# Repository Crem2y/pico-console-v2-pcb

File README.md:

# Pico console V2 Board

A custom handheld console platform built around dual RP2350 microcontrollers, featuring a dedicated main processor and southbridge.

The board integrates a display, audio system, game controls, sensors, and external interfaces, with communication between the two MCUs.

**Note:** This board requires a separate [RP2350A Main Board](https://github.com/Crem2y/rp2350a_main_board) to operate.

## Specifications

- **Main MCU:** Raspberry Pi RP2350A
- **Southbridge MCU:** Raspberry Pi RP2350B
- **Flash:** 1-16 MB
- **Display:** 480x320 LCD with touch panel
- **Audio:** Stereo speakers, 3.5 mm audio jack
- **Controls:** Dual analog sticks, D-pad, face buttons, and additional function buttons
- **Sensors:** 6-axis IMU
- **Haptics:** Dual LRA actuators
- **Communication:** UART-based inter-MCU communication
- **External interfaces:** IR transceiver, Qwiic/ST connector
- **Expansion:** 10-pin FPC connector (0.5 mm pitch), additional GPIO/ADC pads
- **Power inputs:** VUSB (1.8-5.5 V), BAT (3.0-4.2 V)
- **Debug:** SWD interfaces

## Pinout

## Schematics

# PCB

## Design Files

- **EDA:** KiCad 9.0
- PCB design and schematic source files are available in this repository.

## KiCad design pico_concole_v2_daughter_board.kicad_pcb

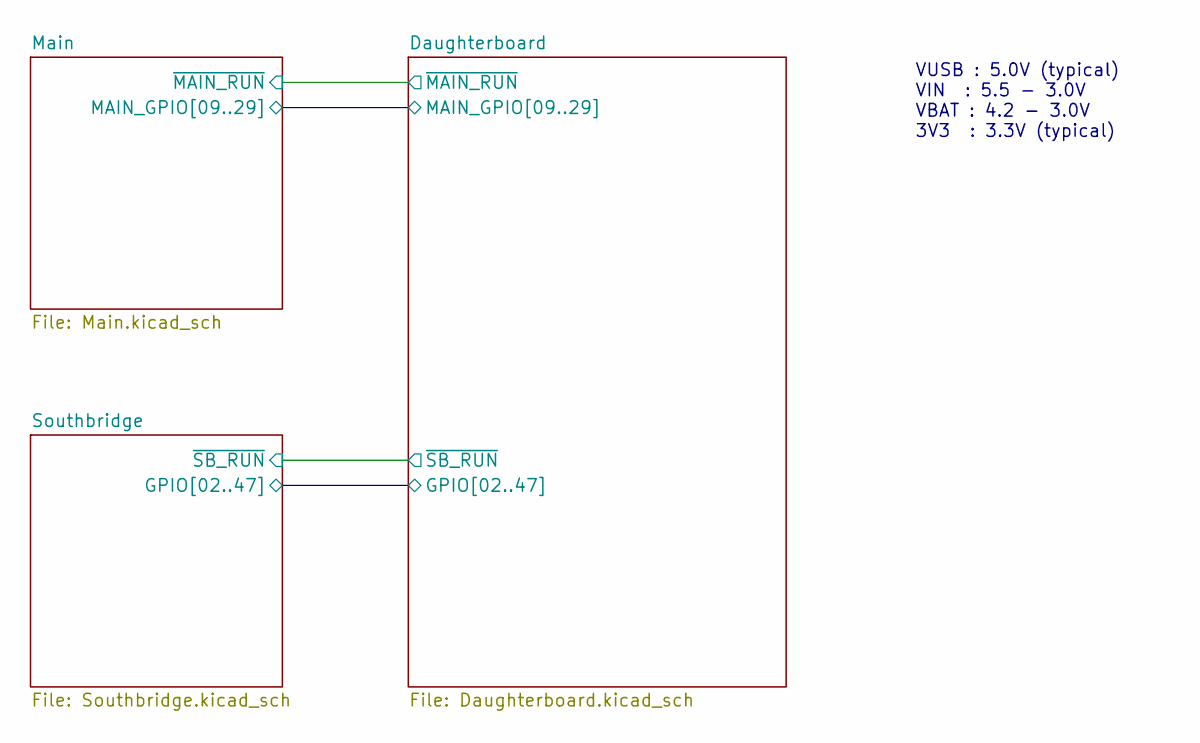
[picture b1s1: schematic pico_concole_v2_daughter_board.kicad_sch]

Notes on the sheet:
VUSB : 5.0V (typical) VIN : 5.5 - 3.0V VBAT : 4.2 - 3.0V 3V3 : 3.3V (typical)

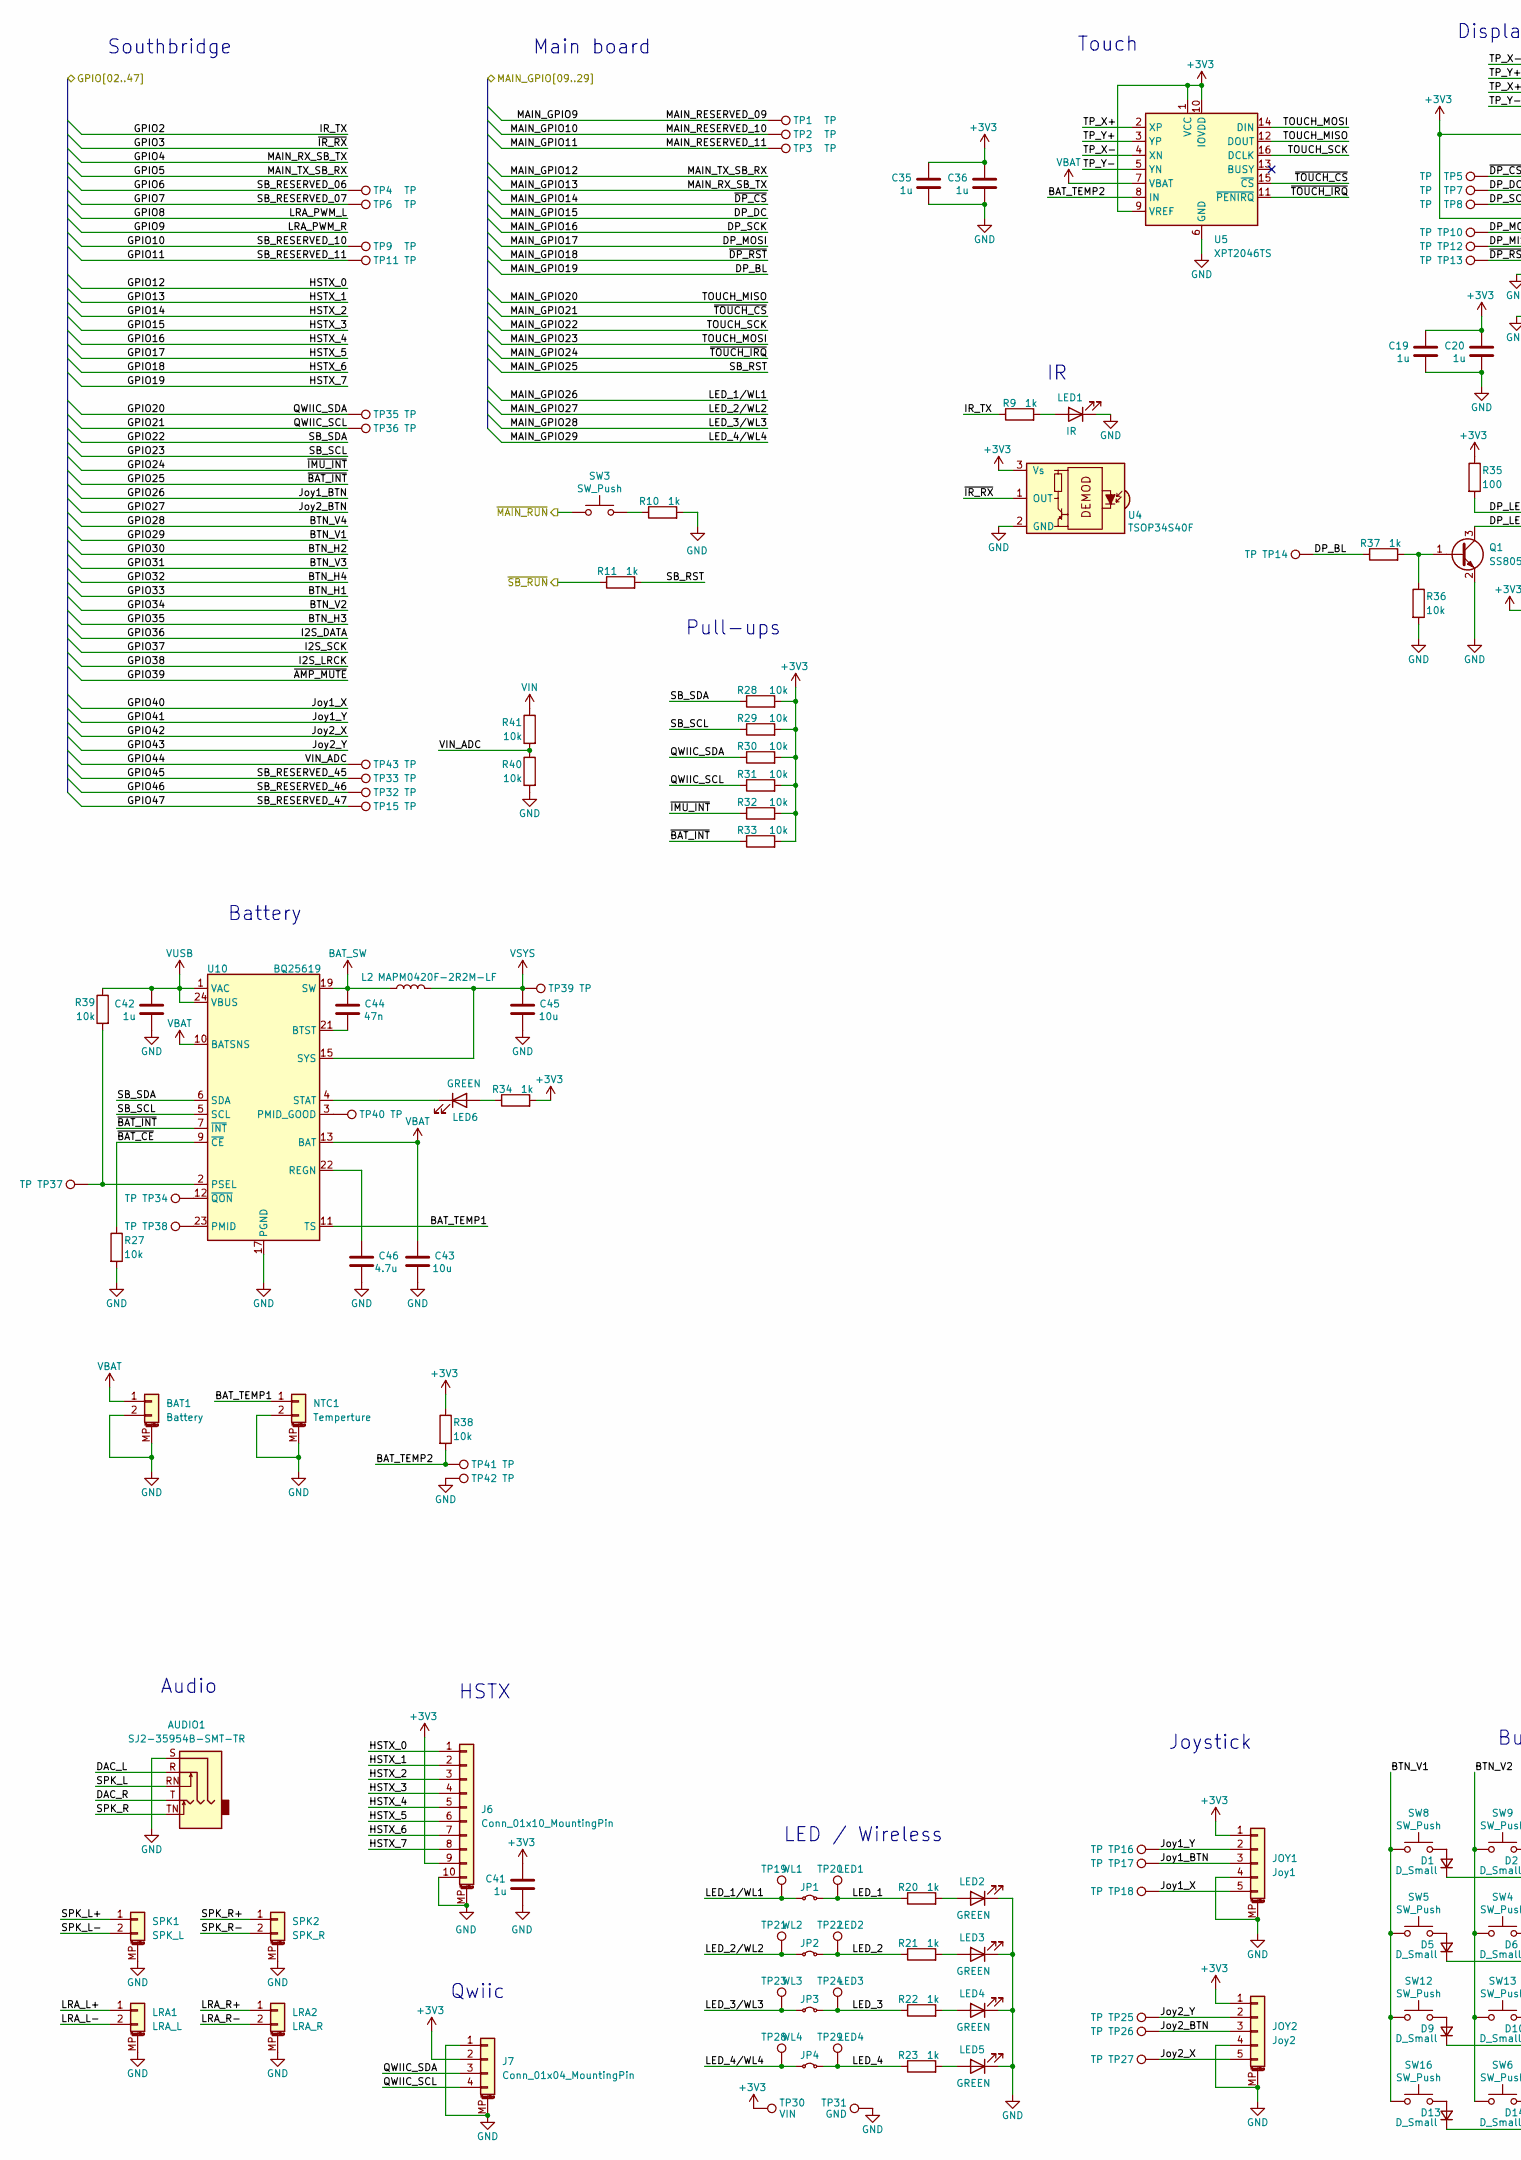
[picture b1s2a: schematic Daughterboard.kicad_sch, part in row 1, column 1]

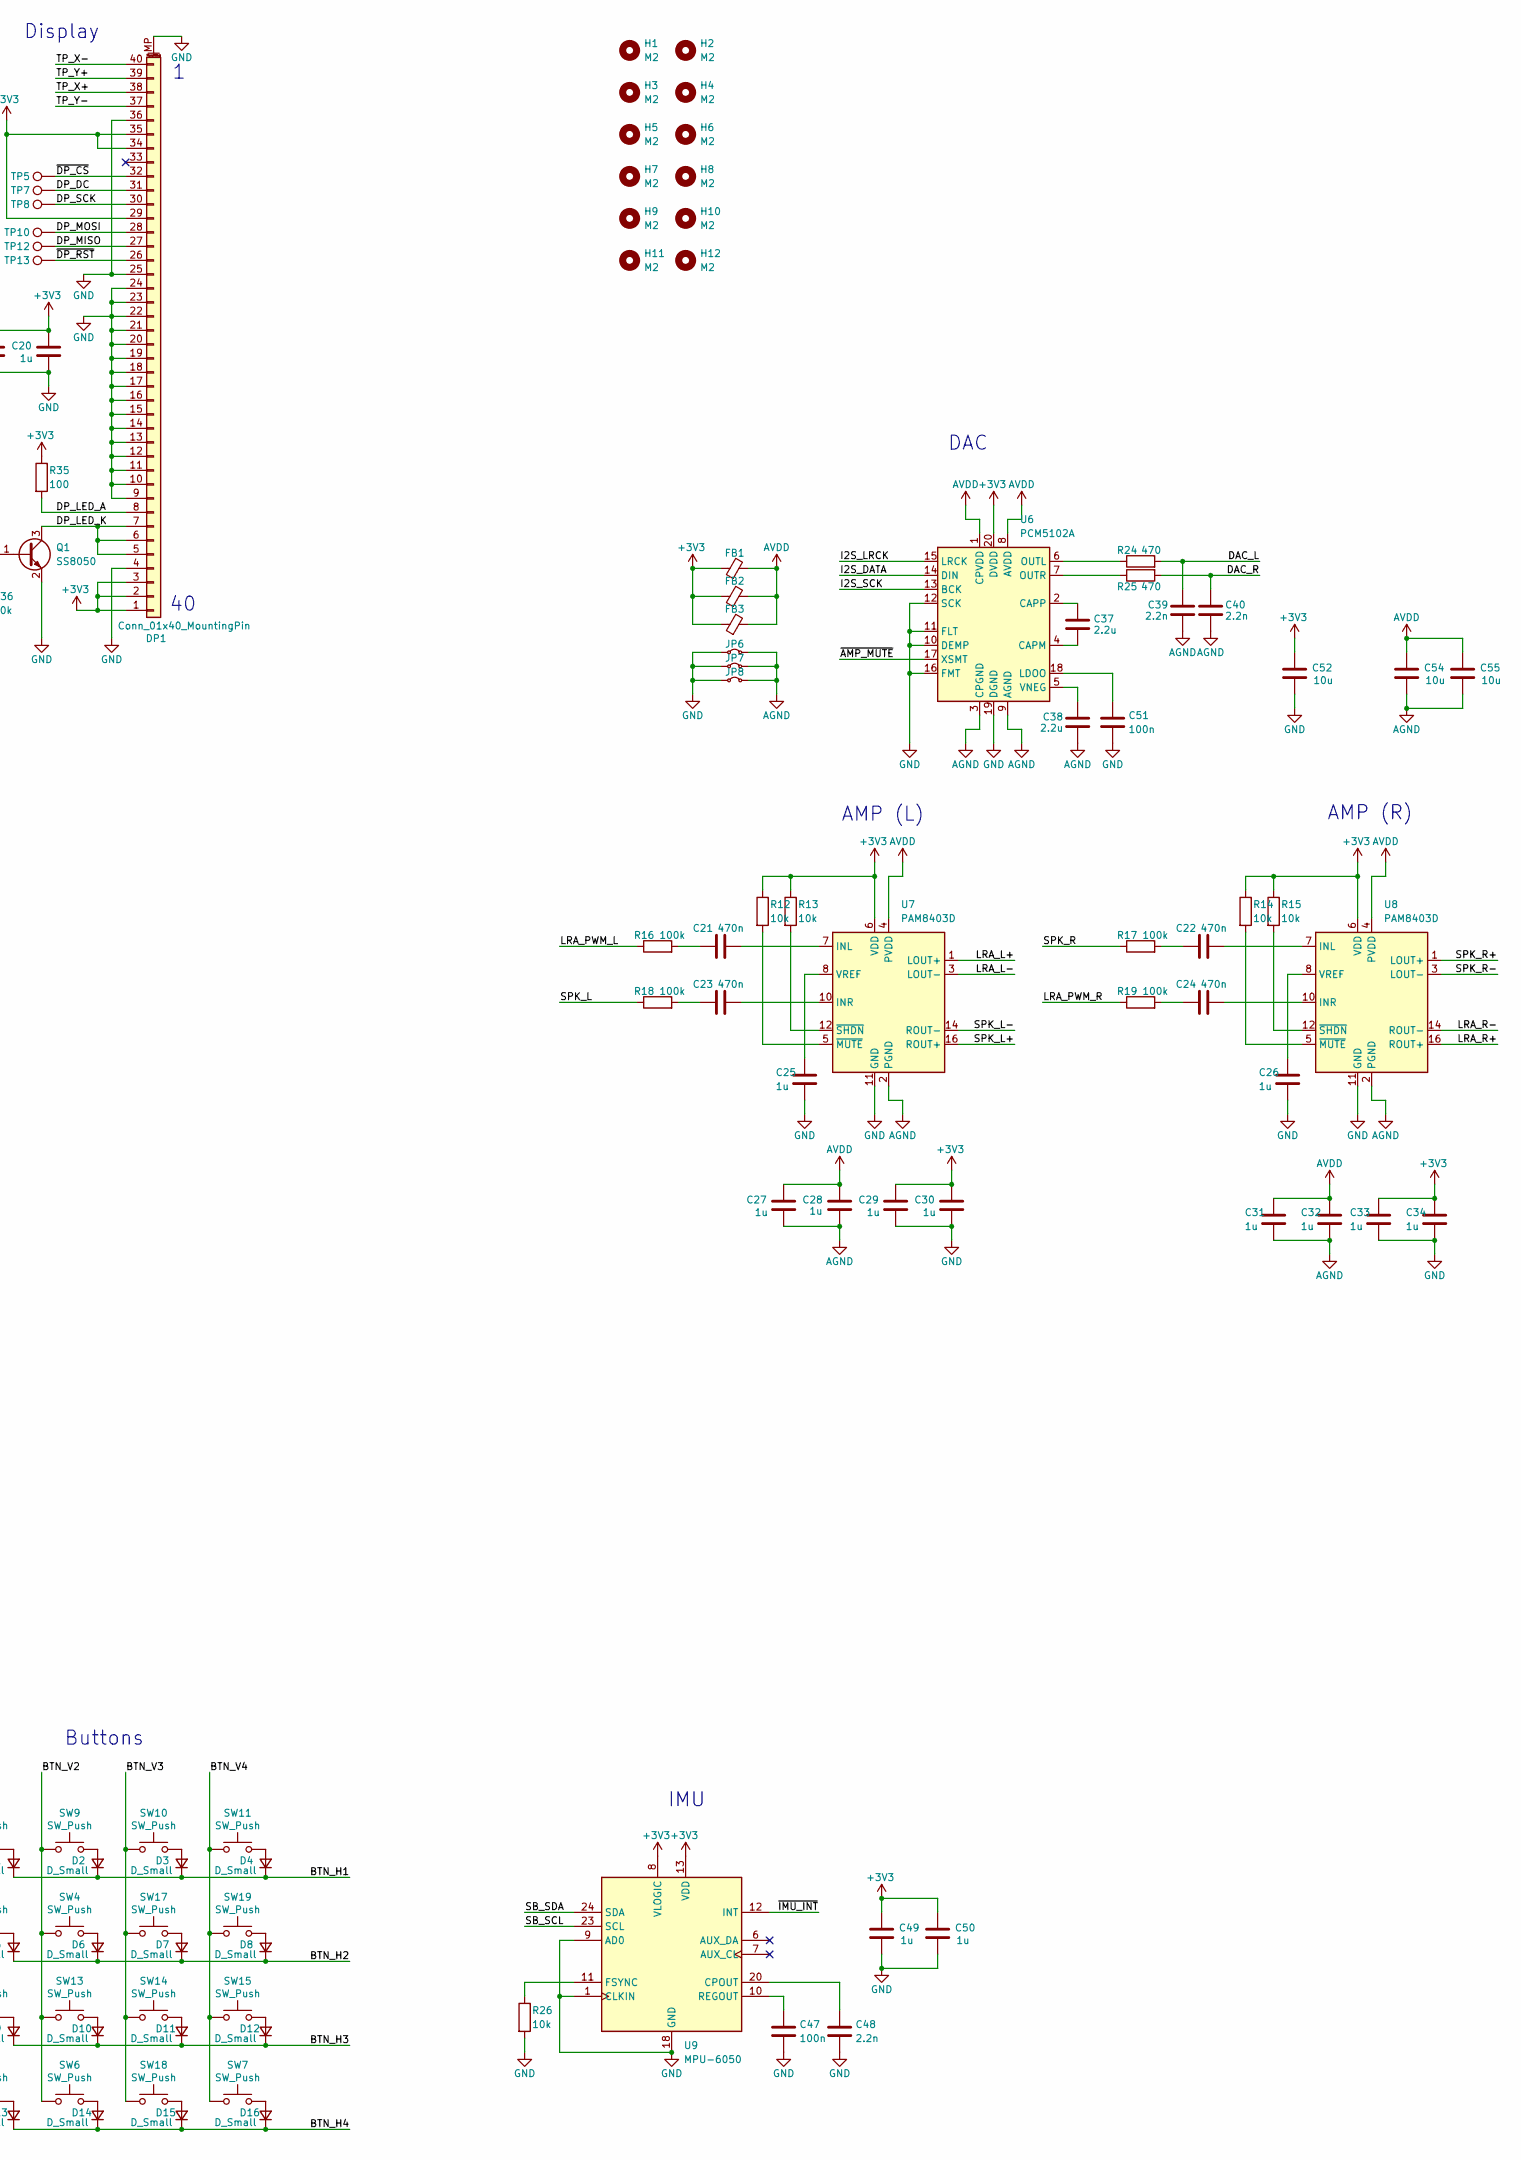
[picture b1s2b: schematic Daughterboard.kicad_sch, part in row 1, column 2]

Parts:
AUDIO1: SJ2-35954B-SMT-TR; Jack_3.5mm_CUI_SJ2-3593D-SMT_Horizontal
BAT1: Battery; Molex_PicoBlade_53261-0271_1x02-1MP_P1.25mm_Horizontal; LCSC PN C177225
C19, C20, C25, C26, C27, C28, C29, C30, C31, C32, C33, C34, C35, C36, C41, C42, C49, C50: 1u; C_0402_1005Metric_Pad0.74x0.62mm_HandSolder
C21, C22, C23, C24: 470n; C_0402_1005Metric_Pad0.74x0.62mm_HandSolder
C37, C38: 2.2u; C_0402_1005Metric_Pad0.74x0.62mm_HandSolder
C39, C40, C48: 2.2n; C_0402_1005Metric_Pad0.74x0.62mm_HandSolder
C43, C45, C52, C54, C55: 10u; C_0402_1005Metric_Pad0.74x0.62mm_HandSolder
C44: 47n; C_0402_1005Metric_Pad0.74x0.62mm_HandSolder
C46: 4.7u; C_0402_1005Metric_Pad0.74x0.62mm_HandSolder
C47, C51: 100n; C_0402_1005Metric_Pad0.74x0.62mm_HandSolder
D1, D2, D3, D4, D5, D6, D7, D8, D9, D10, D11, D12, D13, D14, D15, D16: D_Small; D_0805_2012Metric_Pad1.15x1.40mm_HandSolder
DP1: Conn_01x40_MountingPin; Amphenol_F32Q-1A7x1-11040_1x40-1MP_P0.5mm_Horizontal
FB1, FB2, FB3: FerriteBead_Small; L_0805_2012Metric_Pad1.15x1.40mm_HandSolder
H1, H2, H3, H4, H5, H6, H7, H8, H9, H10, H11, H12: M2; MountingHole_2.2mm_M2
J6: Conn_01x10_MountingPin; TE_1-1734839-0_1x10-1MP_P0.5mm_Horizontal
J7: Conn_01x04_MountingPin; JST_SH_SM04B-SRSS-TB_1x04-1MP_P1.00mm_Horizontal; LCSC PN C160404
JOY1: Joy1; TE_0-1734839-5_1x05-1MP_P0.5mm_Horizontal
JOY2: Joy2; TE_0-1734839-5_1x05-1MP_P0.5mm_Horizontal
JP1, JP2, JP3, JP4: Jumper_2_Small_Bridged; SolderJumper-2_P1.3mm_Bridged_RoundedPad1.0x1.5mm
JP6, JP7, JP8: Jumper_2_Small_Bridged; SolderJumper-2_P1.3mm_Bridged_Pad1.0x1.5mm
L2: MAPM0420F-2R2M-LF; Inductor_SMD_L_4.9x4.4_H2
LED1: IR; LED_D5.0mm_Horizontal_O1.27mm_Z3.0mm_Clear
LED2, LED3, LED4, LED5, LED6: GREEN; LED_0805_2012Metric_Pad1.15x1.40mm_HandSolder
LRA1: LRA_L; Molex_PicoBlade_53261-0271_1x02-1MP_P1.25mm_Horizontal; LCSC PN C177225
LRA2: LRA_R; Molex_PicoBlade_53261-0271_1x02-1MP_P1.25mm_Horizontal; LCSC PN C177225
NTC1: Temperture; Molex_PicoBlade_53261-0271_1x02-1MP_P1.25mm_Horizontal; LCSC PN C177225
Q1: SS8050; SOT-23
R9, R10, R11, R20, R21, R22, R23, R34, R37: 1k; R_0402_1005Metric_Pad0.72x0.64mm_HandSolder
R12, R13, R14, R15, R26, R27, R28, R29, R30, R31, R32, R33, R36, R38, R39, R40, R41: 10k; R_0402_1005Metric_Pad0.72x0.64mm_HandSolder
R16, R17, R18, R19: 100k; R_0402_1005Metric_Pad0.72x0.64mm_HandSolder
R24, R25: 470; R_0402_1005Metric_Pad0.72x0.64mm_HandSolder
R35: 100; R_0402_1005Metric_Pad0.72x0.64mm_HandSolder
SPK1: SPK_L; Molex_PicoBlade_53261-0271_1x02-1MP_P1.25mm_Horizontal; LCSC PN C177225
SPK2: SPK_R; Molex_PicoBlade_53261-0271_1x02-1MP_P1.25mm_Horizontal; LCSC PN C177225
SW3: SW_Push; SW_Push_1P1T_NO_Vertical_Wuerth_434133025816
SW4, SW6: SW_Push; SM-05H-0xC-Zippy
SW5, SW7: SW_Push; SM-05H-0xD-Zippy
SW8, SW9, SW10, SW11, SW12, SW13, SW14, SW15, SW16, SW17, SW18, SW19: SW_Push; SW_PUSH_6mm_H7.3mm
TP1, TP2, TP3, TP4, TP5, TP6, TP7, TP8, TP9, TP10, TP11, TP12, TP13, TP14, TP15, TP16, TP17, TP18, TP25, TP26, TP27, TP32, TP33, TP34, TP35, TP36, TP37, TP38, TP39, TP40, TP41, TP42, TP43: TP; TestPoint_Pad_D1.0mm
TP19: WL1; TestPoint_Pad_1.0x1.0mm
TP20: LED1; TestPoint_Pad_1.0x1.0mm
TP21: WL2; TestPoint_Pad_1.0x1.0mm
TP22: LED2; TestPoint_Pad_1.0x1.0mm
TP23: WL3; TestPoint_Pad_1.0x1.0mm
TP24: LED3; TestPoint_Pad_1.0x1.0mm
TP28: WL4; TestPoint_Pad_1.0x1.0mm
TP29: LED4; TestPoint_Pad_1.0x1.0mm
TP30: VIN; TestPoint_Pad_1.0x1.0mm
TP31: GND; TestPoint_Pad_1.0x1.0mm
U4: TSOP34S40F; Vishay_MOLD-3Pin
U5: XPT2046TS; TSSOP-16_4.4x5mm_P0.65mm
U6: PCM5102A; TSSOP-20_4.4x6.5mm_P0.65mm
U7, U8: PAM8403D; SOIC-16_3.9x9.9mm_P1.27mm
U9: MPU-6050; InvenSense_QFN-24_4x4mm_P0.5mm
U10: BQ25619; Texas_RTW_WQFN-24-1EP_4x4mm_P0.5mm_EP2.7x2.7mm

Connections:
+3V3: C19.1, C20.1, C29.1, C30.1, C33.1, C34.1, C35.1, C36.1, C41.1, C49.1, C50.1, C52.1, DP1.1, DP1.2, DP1.3, DP1.29, DP1.34, DP1.35, FB1.1, FB2.1, FB3.1, J6.9, J7.2, JOY1.1, JOY2.1, R12.1, R13.1, R14.1, R15.1, R28.2, R29.2, R30.2, R31.2, R32.2, R33.2, R34.2, R35.1, R38.1, TP30.1, U4.3 (Vs), U5.1 (VCC), U5.9 (VREF), U5.10 (IOVDD), U6.20 (DVDD), U7.6 (VDD), U8.6 (VDD), U9.8 (VLOGIC), U9.13 (VDD); also elsewhere on the board
/Daughterboard/BAT_TEMP1: NTC1.1, U10.11 (TS)
/Daughterboard/BAT_TEMP2: R38.2, TP41.1, U5.8 (IN)
/Daughterboard/DAC_L: AUDIO1.R, C39.2, R24.2
/Daughterboard/DAC_R: AUDIO1.T, C40.2, R25.2
/Daughterboard/DP_LED_A: DP1.8, R35.2
/Daughterboard/DP_LED_K: DP1.5, DP1.6, DP1.7, Q1.3 (C)
/Daughterboard/DP_MISO: DP1.27, TP12.1
/Daughterboard/GPIO2: R9.1; also elsewhere on the board
/Daughterboard/GPIO3: U4.1 (OUT); also elsewhere on the board
/Daughterboard/GPIO6: TP4.1; also elsewhere on the board
/Daughterboard/GPIO7: TP6.1; also elsewhere on the board
/Daughterboard/GPIO8: R16.1; also elsewhere on the board
/Daughterboard/GPIO9: R19.1; also elsewhere on the board
/Daughterboard/GPIO10: TP9.1; also elsewhere on the board
/Daughterboard/GPIO11: TP11.1; also elsewhere on the board
/Daughterboard/GPIO12: J6.1; also elsewhere on the board
/Daughterboard/GPIO13: J6.2; also elsewhere on the board
/Daughterboard/GPIO14: J6.3; also elsewhere on the board
/Daughterboard/GPIO15: J6.4; also elsewhere on the board
/Daughterboard/GPIO16: J6.5; also elsewhere on the board
/Daughterboard/GPIO17: J6.6; also elsewhere on the board
/Daughterboard/GPIO18: J6.7; also elsewhere on the board
/Daughterboard/GPIO19: J6.8; also elsewhere on the board
/Daughterboard/GPIO20: J7.3, R30.1, TP35.1; also elsewhere on the board
/Daughterboard/GPIO21: J7.4, R31.1, TP36.1; also elsewhere on the board
/Daughterboard/GPIO22: R28.1, U9.24 (SDA), U10.6 (SDA); also elsewhere on the board
/Daughterboard/GPIO23: R29.1, U9.23 (SCL), U10.5 (SCL); also elsewhere on the board
/Daughterboard/GPIO24: R32.1, U9.12 (INT); also elsewhere on the board
/Daughterboard/GPIO25: R33.1, U10.7 (~INT); also elsewhere on the board
/Daughterboard/GPIO26: JOY1.3, TP17.1; also elsewhere on the board
/Daughterboard/GPIO27: JOY2.3, TP26.1; also elsewhere on the board
/Daughterboard/GPIO28: SW7.1, SW11.1, SW15.1, SW19.1; also elsewhere on the board
/Daughterboard/GPIO29: SW5.1, SW8.1, SW12.1, SW16.1; also elsewhere on the board
/Daughterboard/GPIO30: D5.1 (K), D6.1 (K), D7.1 (K), D8.1 (K); also elsewhere on the board
/Daughterboard/GPIO31: SW10.1, SW14.1, SW17.1, SW18.1; also elsewhere on the board
/Daughterboard/GPIO32: D13.1 (K), D14.1 (K), D15.1 (K), D16.1 (K); also elsewhere on the board
/Daughterboard/GPIO33: D1.1 (K), D2.1 (K), D3.1 (K), D4.1 (K); also elsewhere on the board
/Daughterboard/GPIO34: SW4.1, SW6.1, SW9.1, SW13.1; also elsewhere on the board
/Daughterboard/GPIO35: D9.1 (K), D10.1 (K), D11.1 (K), D12.1 (K); also elsewhere on the board
/Daughterboard/GPIO36: U6.14 (DIN); also elsewhere on the board
/Daughterboard/GPIO37: U6.13 (BCK); also elsewhere on the board
/Daughterboard/GPIO38: U6.15 (LRCK); also elsewhere on the board
/Daughterboard/GPIO39: U6.17 (XSMT); also elsewhere on the board
/Daughterboard/GPIO40: JOY1.5, TP18.1; also elsewhere on the board
/Daughterboard/GPIO41: JOY1.2, TP16.1; also elsewhere on the board
/Daughterboard/GPIO42: JOY2.5, TP27.1; also elsewhere on the board
/Daughterboard/GPIO43: JOY2.2, TP25.1; also elsewhere on the board
/Daughterboard/GPIO44: R40.1, R41.2, TP43.1; also elsewhere on the board
/Daughterboard/GPIO45: TP33.1; also elsewhere on the board
/Daughterboard/GPIO46: TP32.1; also elsewhere on the board
/Daughterboard/GPIO47: TP15.1; also elsewhere on the board
/Daughterboard/LED_1: JP1.2 (B), R20.1, TP20.1
/Daughterboard/LED_2: JP2.2 (B), R21.1, TP22.1
/Daughterboard/LED_3: JP3.2 (B), R22.1, TP24.1
/Daughterboard/LED_4: JP4.2 (B), R23.1, TP29.1
/Daughterboard/LRA_L+: LRA1.1, U7.1 (LOUT+)
/Daughterboard/LRA_L-: LRA1.2, U7.3 (LOUT-)
/Daughterboard/LRA_R+: LRA2.1, U8.16 (ROUT+)
/Daughterboard/LRA_R-: LRA2.2, U8.14 (ROUT-)
/Daughterboard/MAIN_GPIO9: TP1.1; also elsewhere on the board
/Daughterboard/MAIN_GPIO10: TP2.1; also elsewhere on the board
/Daughterboard/MAIN_GPIO11: TP3.1; also elsewhere on the board
/Daughterboard/MAIN_GPIO14: DP1.32, TP5.1; also elsewhere on the board
/Daughterboard/MAIN_GPIO15: DP1.31, TP7.1; also elsewhere on the board
/Daughterboard/MAIN_GPIO16: DP1.30, TP8.1; also elsewhere on the board
/Daughterboard/MAIN_GPIO17: DP1.28, TP10.1; also elsewhere on the board
/Daughterboard/MAIN_GPIO18: DP1.26, TP13.1; also elsewhere on the board
/Daughterboard/MAIN_GPIO19: R37.1, TP14.1; also elsewhere on the board
/Daughterboard/MAIN_GPIO20: U5.12 (DOUT); also elsewhere on the board
/Daughterboard/MAIN_GPIO21: U5.15 (~CS); also elsewhere on the board
/Daughterboard/MAIN_GPIO22: U5.16 (DCLK); also elsewhere on the board
/Daughterboard/MAIN_GPIO23: U5.14 (DIN); also elsewhere on the board
/Daughterboard/MAIN_GPIO24: U5.11 (~PENIRQ); also elsewhere on the board
/Daughterboard/MAIN_GPIO25: R11.2; also elsewhere on the board
/Daughterboard/MAIN_GPIO26: JP1.1 (A), TP19.1; also elsewhere on the board
/Daughterboard/MAIN_GPIO27: JP2.1 (A), TP21.1; also elsewhere on the board
/Daughterboard/MAIN_GPIO28: JP3.1 (A), TP23.1; also elsewhere on the board
/Daughterboard/MAIN_GPIO29: JP4.1 (A), TP28.1; also elsewhere on the board
/Daughterboard/SPK_L: AUDIO1.RN, R18.1
/Daughterboard/SPK_L+: SPK1.1, U7.16 (ROUT+)
/Daughterboard/SPK_L-: SPK1.2, U7.14 (ROUT-)
/Daughterboard/SPK_R: AUDIO1.TN, R17.1
/Daughterboard/SPK_R+: SPK2.1, U8.1 (LOUT+)
/Daughterboard/SPK_R-: SPK2.2, U8.3 (LOUT-)
/Daughterboard/TP_X+: DP1.38, U5.2 (XP)
/Daughterboard/TP_X-: DP1.40, U5.4 (XN)
/Daughterboard/TP_Y+: DP1.39, U5.3 (YP)
/Daughterboard/TP_Y-: DP1.37, U5.5 (YN)
/Daughterboard/~BAT_CE: R27.1, U10.9 (~CE)
/Daughterboard/~MAIN_RUN: SW3.1; also elsewhere on the board
/Daughterboard/~SB_RUN: R11.1; also elsewhere on the board
AGND: C27.2, C28.2, C31.2, C32.2, C38.2, C39.1, C40.1, C54.2, C55.2, JP6.2 (B), JP7.2 (B), JP8.2 (B), U6.3 (CPGND), U6.9 (AGND), U7.2 (PGND), U7.15 (PGND), U8.2 (PGND), U8.15 (PGND)
AVDD: C27.1, C28.1, C31.1, C32.1, C54.1, C55.1, FB1.2, FB2.2, FB3.2, U6.1 (CPVDD), U6.8 (AVDD), U7.4 (PVDD), U7.13 (PVDD), U8.4 (PVDD), U8.13 (PVDD)
BAT_SW: C44.1, L2.1, U10.19 (SW), U10.20 (SW)
GND: AUDIO1.S, BAT1.2, BAT1.MP (MountPin), C19.2, C20.2, C25.2, C26.2, C29.2, C30.2, C33.2, C34.2, C35.2, C36.2, C41.2, C42.2, C43.2, C45.2, C46.2, C47.2, C48.2, C49.2, C50.2, C51.2, C52.2, DP1.4, DP1.9, DP1.10, DP1.11, DP1.12, DP1.13, DP1.14, DP1.15, DP1.16, DP1.17, DP1.18, DP1.19, DP1.20, DP1.21, DP1.22, DP1.23, DP1.24, DP1.25, DP1.36, DP1.MP (MountPin), J6.10, J6.MP (MountPin), J7.1, J7.MP (MountPin), JOY1.4, JOY1.MP (MountPin), JOY2.4, JOY2.MP (MountPin), JP6.1 (A), JP7.1 (A), JP8.1 (A), LED1.1 (K), LED2.1 (K), LED3.1 (K), LED4.1 (K), LED5.1 (K), LRA1.MP (MountPin), LRA2.MP (MountPin), NTC1.2, NTC1.MP (MountPin), Q1.2 (E), R10.2, R26.2, R27.2, R36.2, R40.2, SPK1.MP (MountPin), SPK2.MP (MountPin), TP31.1, TP42.1, U4.2 (GND), U5.6 (GND), U6.10 (DEMP), U6.11 (FLT), U6.12 (SCK), U6.16 (FMT), U6.19 (DGND), U7.11 (GND), U8.11 (GND), U9.1 (CLKIN), U9.9 (AD0), U9.18 (GND), U10.17 (PGND), U10.18 (PGND), U10.25 (PGND); also elsewhere on the board
unnamed: C21.1, R16.2
unnamed: C22.1, R17.2
unnamed: C23.1, R18.2
unnamed: C24.1, R19.2
unnamed: D1.2 (A), SW8.2
unnamed: D2.2 (A), SW9.2
unnamed: D3.2 (A), SW10.2
unnamed: D4.2 (A), SW11.2
unnamed: D5.2 (A), SW5.2
unnamed: D6.2 (A), SW4.2
unnamed: D7.2 (A), SW17.2
unnamed: D8.2 (A), SW19.2
unnamed: D9.2 (A), SW12.2
unnamed: D10.2 (A), SW13.2
unnamed: D11.2 (A), SW14.2
unnamed: D12.2 (A), SW15.2
unnamed: D13.2 (A), SW16.2
unnamed: D14.2 (A), SW6.2
unnamed: D15.2 (A), SW18.2
unnamed: D16.2 (A), SW7.2
unnamed: LED1.2 (A), R9.2
unnamed: LED2.2 (A), R20.2
unnamed: LED3.2 (A), R21.2
unnamed: LED4.2 (A), R22.2
unnamed: LED5.2 (A), R23.2
unnamed: LED6.2 (A), R34.1
unnamed: LED6.1 (K), U10.4 (STAT)
unnamed: Q1.1 (B), R36.1, R37.2
unnamed: R10.1, SW3.2
unnamed: C37.2, U6.4 (CAPM)
unnamed: C37.1, U6.2 (CAPP)
unnamed: C51.1, U6.18 (LDOO)
unnamed: R24.1, U6.6 (OUTL)
unnamed: R25.1, U6.7 (OUTR)
unnamed: C38.1, U6.5 (VNEG)
unnamed: C21.2, U7.7 (INL)
unnamed: C23.2, U7.10 (INR)
unnamed: C25.1, U7.8 (VREF)
unnamed: R12.2, U7.5 (~MUTE)
unnamed: R13.2, U7.12 (~SHDN)
unnamed: C22.2, U8.7 (INL)
unnamed: C24.2, U8.10 (INR)
unnamed: C26.1, U8.8 (VREF)
unnamed: R14.2, U8.5 (~MUTE)
unnamed: R15.2, U8.12 (~SHDN)
unnamed: C48.1, U9.20 (CPOUT)
unnamed: R26.1, U9.11 (FSYNC)
unnamed: C47.1, U9.10 (REGOUT)
unnamed: C44.2, U10.21 (BTST)
unnamed: TP38.1, U10.23 (PMID)
unnamed: TP40.1, U10.3 (PMID_GOOD)
unnamed: R39.2, TP37.1, U10.2 (PSEL)
unnamed: C46.1, U10.22 (REGN)
unnamed: TP34.1, U10.12 (~QON)
VBAT: BAT1.1, C43.1, U5.7 (VBAT), U10.10 (BATSNS), U10.13 (BAT), U10.14 (BAT); also elsewhere on the board
VIN: R41.1; also elsewhere on the board
VSYS: C45.1, L2.2, TP39.1, U10.15 (SYS), U10.16 (SYS)
VUSB: C42.1, R39.1, U10.1 (VAC), U10.24 (VBUS); also elsewhere on the board

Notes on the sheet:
Touch
DAC
IMU
Southbridge
Audio
LED / Wireless
Qwiic
AMP (R)
Buttons
AMP (L)
Display
Battery
HSTX
Joystick
Main board
Pull-ups

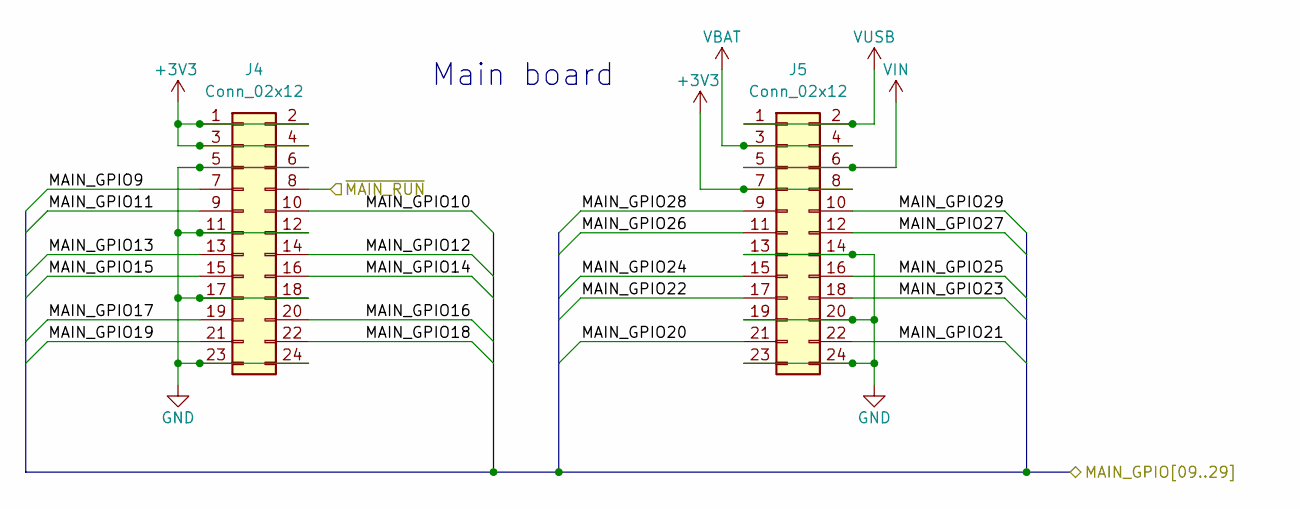
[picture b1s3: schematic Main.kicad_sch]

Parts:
J4, J5: Conn_02x12; PinHeader_2x12_P2.54mm_Vertical_SMD

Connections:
+3V3: J4.1, J4.2, J4.3, J4.4, J5.7, J5.8; also elsewhere on the board
/Daughterboard/MAIN_GPIO9: J4.7; also elsewhere on the board
/Daughterboard/MAIN_GPIO10: J4.10; also elsewhere on the board
/Daughterboard/MAIN_GPIO11: J4.9; also elsewhere on the board
/Daughterboard/MAIN_GPIO12: J4.14; also elsewhere on the board
/Daughterboard/MAIN_GPIO13: J4.13; also elsewhere on the board
/Daughterboard/MAIN_GPIO14: J4.16; also elsewhere on the board
/Daughterboard/MAIN_GPIO15: J4.15; also elsewhere on the board
/Daughterboard/MAIN_GPIO16: J4.20; also elsewhere on the board
/Daughterboard/MAIN_GPIO17: J4.19; also elsewhere on the board
/Daughterboard/MAIN_GPIO18: J4.22; also elsewhere on the board
/Daughterboard/MAIN_GPIO19: J4.21; also elsewhere on the board
/Daughterboard/MAIN_GPIO20: J5.21; also elsewhere on the board
/Daughterboard/MAIN_GPIO21: J5.22; also elsewhere on the board
/Daughterboard/MAIN_GPIO22: J5.17; also elsewhere on the board
/Daughterboard/MAIN_GPIO23: J5.18; also elsewhere on the board
/Daughterboard/MAIN_GPIO24: J5.15; also elsewhere on the board
/Daughterboard/MAIN_GPIO25: J5.16; also elsewhere on the board
/Daughterboard/MAIN_GPIO26: J5.11; also elsewhere on the board
/Daughterboard/MAIN_GPIO27: J5.12; also elsewhere on the board
/Daughterboard/MAIN_GPIO28: J5.9; also elsewhere on the board
/Daughterboard/MAIN_GPIO29: J5.10; also elsewhere on the board
/Daughterboard/~MAIN_RUN: J4.8; also elsewhere on the board
GND: J4.5, J4.6, J4.11, J4.12, J4.17, J4.18, J4.23, J4.24, J5.13, J5.14, J5.19, J5.20, J5.23, J5.24; also elsewhere on the board
VBAT: J5.3, J5.4; also elsewhere on the board
VIN: J5.5, J5.6; also elsewhere on the board
VUSB: J5.1, J5.2; also elsewhere on the board

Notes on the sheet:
Main board
